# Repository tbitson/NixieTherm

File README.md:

# NixieTherm
 An analog nixie Tube Thermometer based on a IN-13 Nixie bar graph tube. Uses a Teensy 3.2 microcontroller to display temperature readings from a DS-18B20 1-wire temperature sensor.
 
 This is a n in-work project!
 
 Major hardware:
 IN-13 Nixie bar-graph tube (ebay.com)
 High voltage power supply module, such as a NCH8200HV 5V to 170V convertor (ebay.com)
 Teensy 3.2 microcontroller (PRJC.com)
 PC Board - eagle files included
 3D printed display mount and spacers - STL files included
 Laser cut acrylic display - laserdraw files included
 ULN2003 IC, RGB Leds, resistors, transistors...

 3D Printed objects available on TinkerCad.com
 https://www.tinkercad.com/things/9rIuJBIbugg-nixietherm/edit

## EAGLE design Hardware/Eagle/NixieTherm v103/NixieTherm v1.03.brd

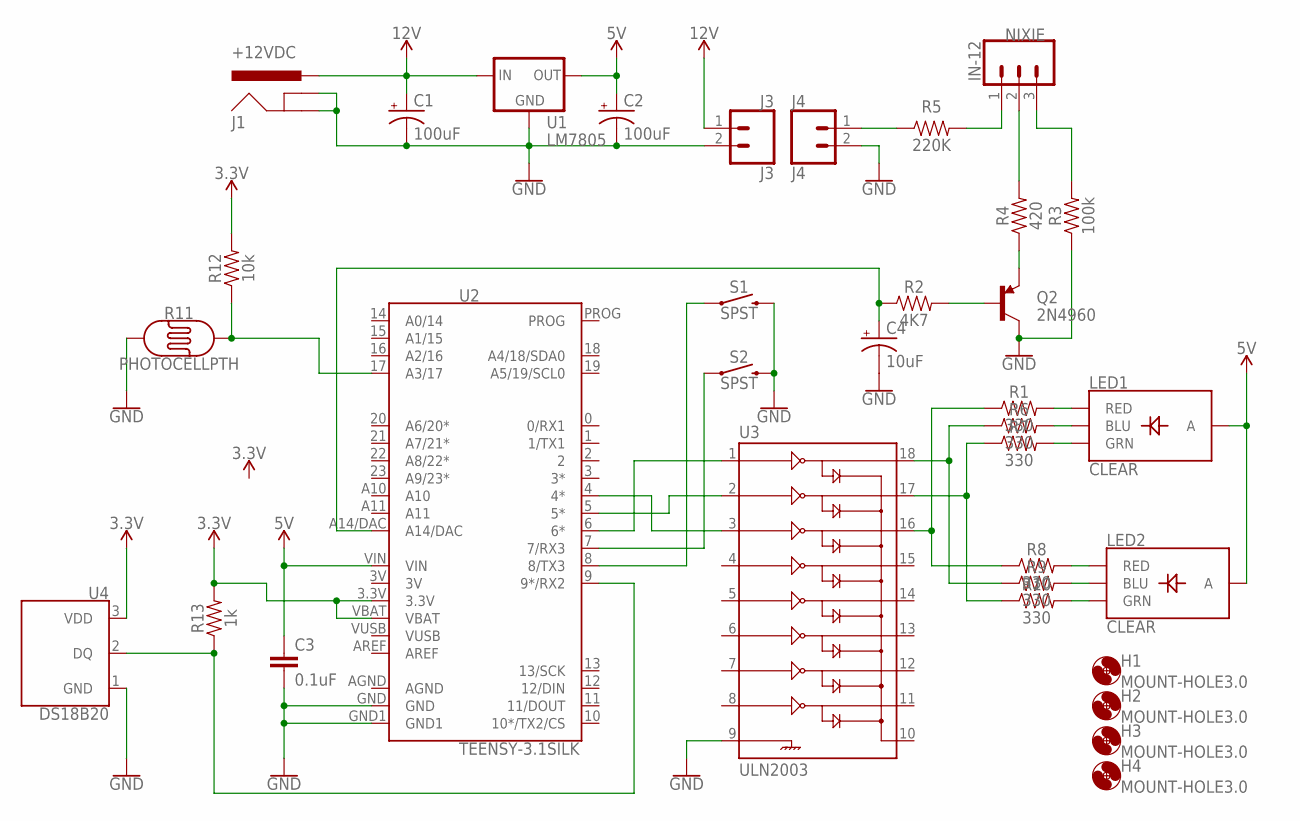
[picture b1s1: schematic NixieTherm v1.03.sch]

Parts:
C1, C2: 100uF; CPOL-RADIAL-2.5MM-6.5MM
C3: 0.1uF; CAP-PTH-SMALL-KIT
C4: 10uF; CPOL-RADIAL-2.5MM-5MM
H1, H2, H3, H4: MOUNT-HOLE3.0; 3,0
J1: +12VDC; POWER_JACK_PTH
J3: J3; 1X02
J4: J4; 1X02
LED1, LED2: CLEAR; LED-RGB-THRU
NIXIE: IN-12; 1X03_NO_SILK
Q2: 2N4960; TO-92
R1, R6, R7, R8, R9, R10: 330; AXIAL-0.3
R2: 4K7; AXIAL-0.3
R3: 100k; AXIAL-0.3
R4: 420; AXIAL-0.3
R5: 220K; AXIAL-0.3
R11: PHOTOCELLPTH; PHOTOCELL
R12: 10k; AXIAL-0.3
R13: 1k; AXIAL-0.3
S1, S2: SPST; TACTILE_SWITCH_PTH_6.0MM
U1: LM7805; TO-220-ALT
U2: TEENSY-3.1SILK; TEENSY-3.1
U3: ULN2003; DIL18
U4: DS18B20; TO-92-AMMO

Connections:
3.3V: R12.P$2 (2), R13.P$2 (2), U2.3.3V, U2.VBAT, U4.3 (VDD)
3V: U2.3V
5V: C2.1 (+), C3.1, LED1.2 (A), LED2.2 (A), U1.OUT, U2.VIN
12V: C1.1 (+), J1.PWR, J3.1, U1.IN
AGND: U2.AGND
GND: C1.2 (-), C2.2 (-), C3.2, C4.2 (-), J1.GND, J1.GNDBREAK, J3.2, J4.2, Q2.3 (C), R3.P$1 (1), R11.1, S1.3 (2), S2.3 (2), U1.GND, U2.GND, U2.GND1, U3.9, U4.1 (GND)
unnamed: R6.P$1 (1), R9.P$1 (1), U3.18
unnamed: R1.P$1 (1), R8.P$1 (1), U3.16
unnamed: R7.P$1 (1), R10.P$1 (1), U3.17
unnamed: NIXIE.1, R5.P$2 (2)
unnamed: NIXIE.3, R3.P$2 (2)
unnamed: NIXIE.2, R4.P$2 (2)
unnamed: Q2.2 (B), R2.P$2 (2)
unnamed: Q2.1 (E), R4.P$1 (1)
unnamed: C4.1 (+), R2.P$1 (1), U2.A14/DAC
unnamed: U2.4 (4*), U3.3
unnamed: U2.5 (5*), U3.2
unnamed: U2.6 (6*), U3.1
unnamed: S2.1, U2.7 (7/RX3)
unnamed: LED1.1 (RED), R1.P$2 (2)
unnamed: S1.1, U2.8 (8/TX3)
unnamed: LED1.4 (BLU), R6.P$2 (2)
unnamed: LED1.3 (GRN), R7.P$2 (2)
unnamed: LED2.1 (RED), R8.P$2 (2)
unnamed: LED2.4 (BLU), R9.P$2 (2)
unnamed: LED2.3 (GRN), R10.P$2 (2)
unnamed: J4.1, R5.P$1 (1)
unnamed: R11.2, R12.P$1 (1), U2.17 (A3/17)
unnamed: R13.P$1 (1), U2.9 (9*/RX2), U4.2 (DQ)
VUSB: U2.VUSB

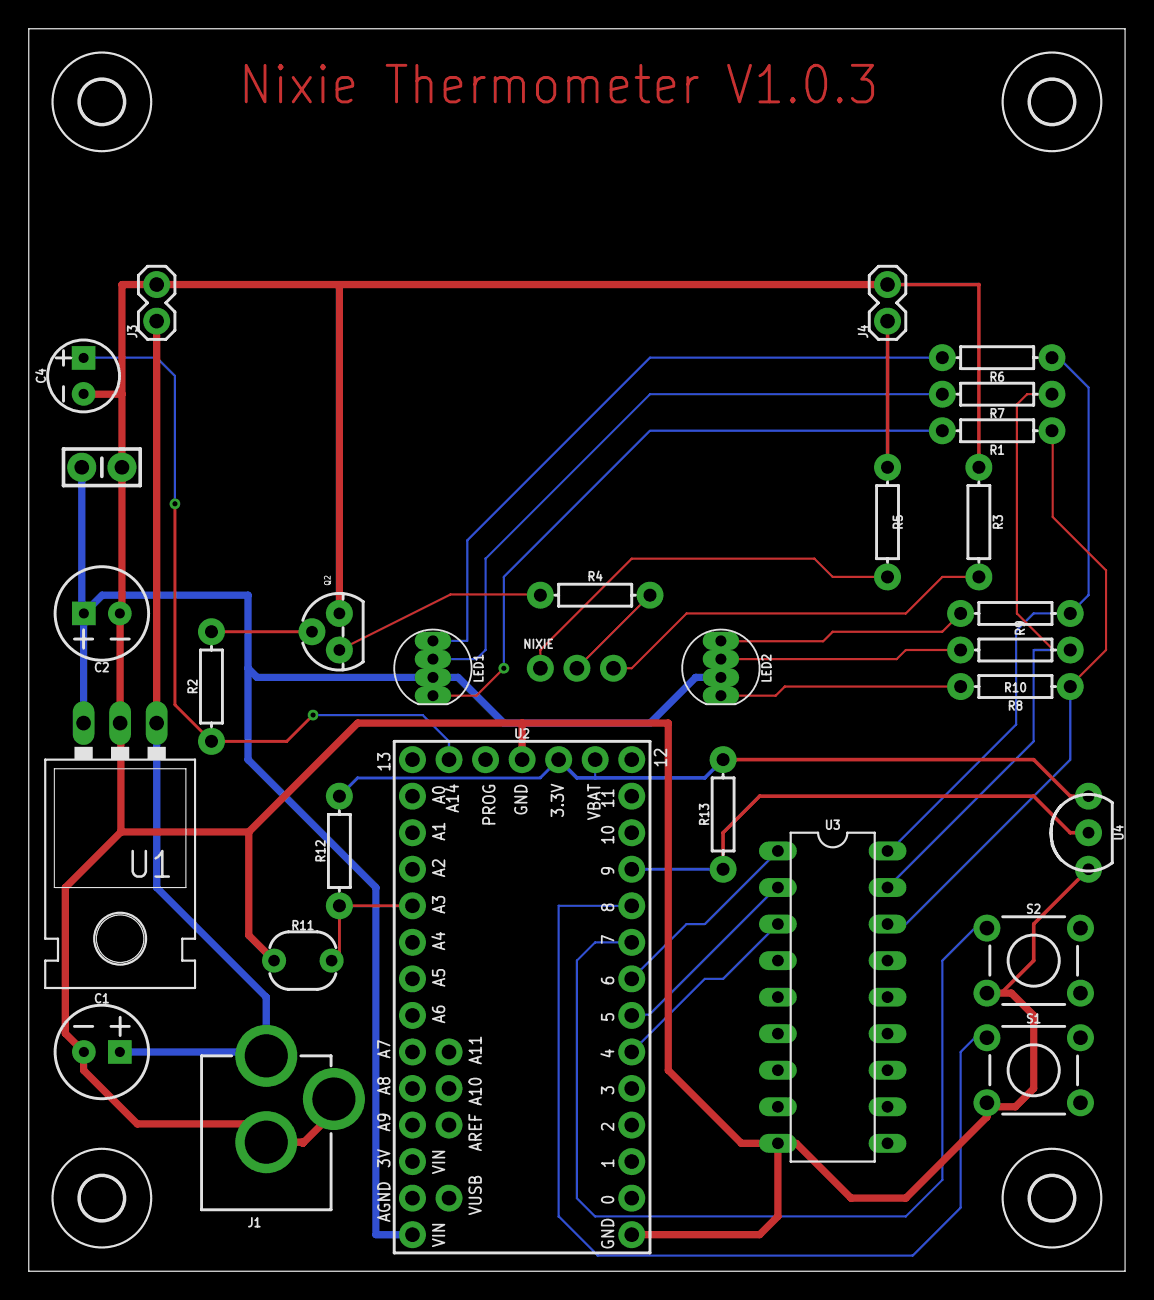
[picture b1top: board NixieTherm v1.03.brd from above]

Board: 2 copper layers, 76.2 x 86.4 mm, 34 parts (0 on the bottom side), 27 nets.

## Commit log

2020-10-01 NixieTherm Initial Release
    An IN-13 Nixie analog bar-graph thermometer.
2020-10-01 Added schematic
    Added schematic and updated readme

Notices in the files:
parts and their libraries:
SparkFun-Boards: Licensing: Creative Commons ShareAlike 4.0 International - https://creativecommons.org/licenses/by-sa/4.0
